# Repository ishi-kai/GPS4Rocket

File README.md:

# GPS System for Rocket
Commercially available GPS systems are not available for rockets.  
Therefore, we have created a full-scratch system.  

## Specification
- GPS Antenna
    - Use commercially available active antennas.
- [GPS Front End](https://github.com/ishi-kai/GPS4Rocket#GPS_FrontEnd)
    - MAX2769B-based GPS front-end board
- [Navigation Message Processor](https://github.com/ishi-kai/GPS4Rocket#Navigation_Message_Processor)
    - Operator to process IO data and navigation messages

## [GPS Front End Board](/GPS_FrontEnd/)
This is the hardware that handles the GPS front end. And This was created with KiCAD 9.  

## [Navigation Message Processor](/Navigation_Message_Processor/)

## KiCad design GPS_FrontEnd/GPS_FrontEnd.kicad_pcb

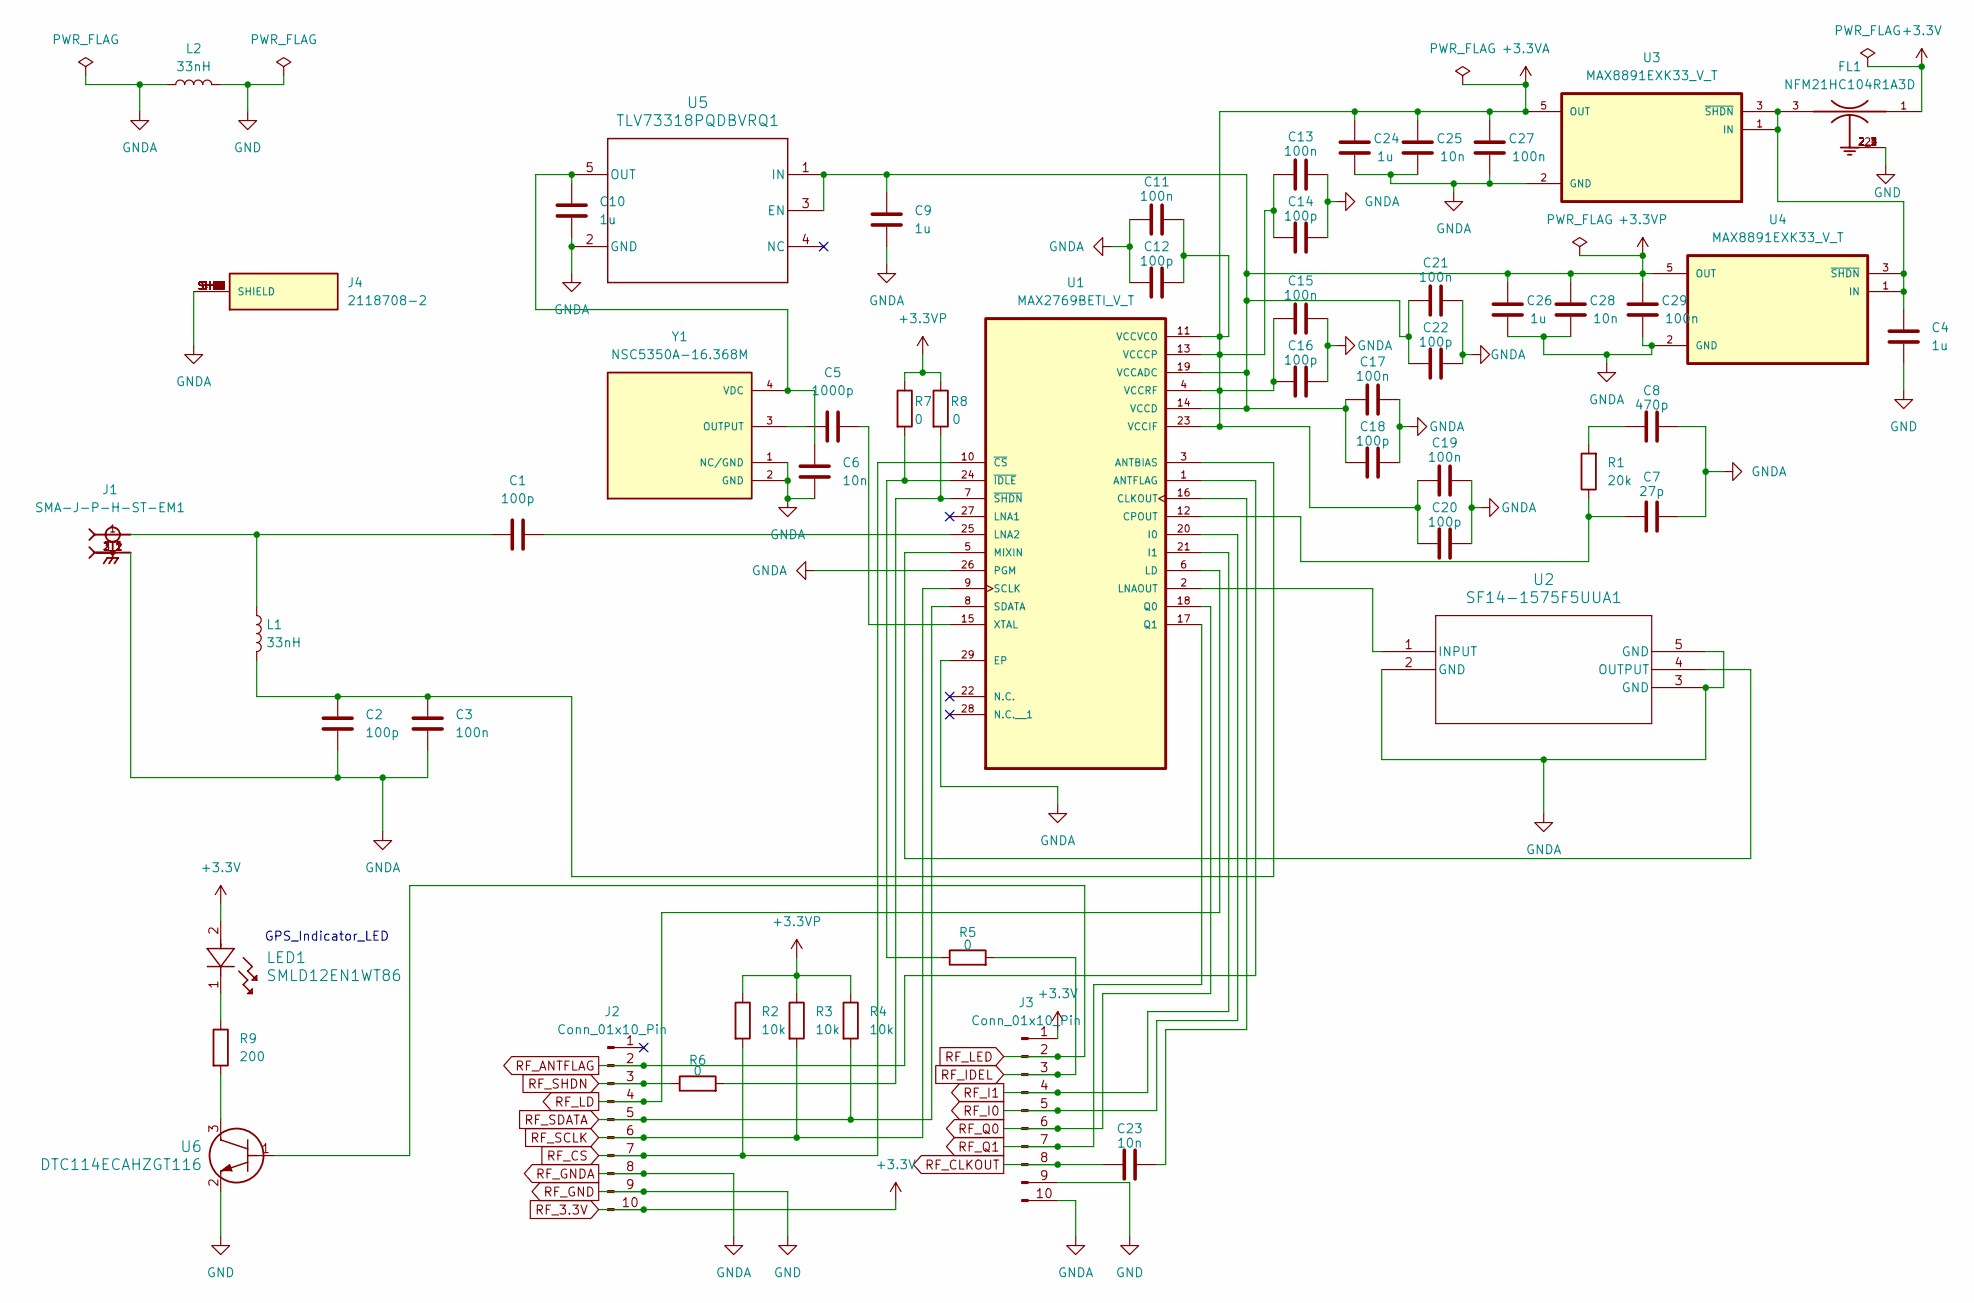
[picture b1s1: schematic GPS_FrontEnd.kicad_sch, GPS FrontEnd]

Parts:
C1, C2, C12, C14, C16, C18, C20, C22: 100p; C_0603_1608Metric
C3: 100n; C_1111_2828Metric
C4, C9, C10, C24, C26: 1u; C_0603_1608Metric
C5: 1000p; C_1210_3225Metric
C6: 10n; C_0505_1313Metric
C7: 27p; C_0603_1608Metric
C8: 470p; C_0505_1313Metric
C11, C13, C15, C17, C19, C21, C27, C29: 100n; C_0603_1608Metric
C23, C25, C28: 10n; C_0603_1608Metric
FL1: NFM21HC104R1A3D; FIL_NFM21HC104R1A3D
J1: SMA-J-P-H-ST-EM1; SAMTEC_SMA-J-P-H-ST-EM1; PARTREV G
J2, J3: Conn_01x10_Pin; PinHeader_1x10_P2.54mm_Vertical
J4: 2118708-2; TE_2118708-2; PARTREV A2
L1, L2: 33nH; L_0603_1608Metric
LED1: SMLD12EN1WT86
R1: 20k; R_0603_1608Metric
R2, R3, R4: 10k; R_0603_1608Metric
R5, R6, R7, R8: 0; R_0603_1608Metric
R9: 200; R_0603_1608Metric
U1: MAX2769BETI_V_T; QFN50P500X500X80-29N
U2: SF14-1575F5UUA1; SO4_1411-SAW_1p1x1p4_KAV
U3, U4: MAX8891EXK33_V_T; SOT65P210X110-5N
U5: TLV73318PQDBVRQ1; DBV0005A_N
U6: DTC114ECAHZGT116; TRANS_DTCZCAHZGT_ROM
Y1: NSC5350A-16.368M; OSC_TX22-18025S-19.200-R; PARTREV Nov 07, 2023

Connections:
+3.3VA: C11.2, C12.2, C13.2, C14.2, C15.1, C16.1, C19.1, C20.1, C24.1, C25.1, C27.1, U1.4 (VCCRF), U1.11 (VCCVCO), U1.13 (VCCCP), U1.23 (VCCIF), U3.5 (OUT)
+3.3VP: C9.1, C17.2, C18.2, C21.1, C22.1, C26.1, C28.1, C29.1, R2.1, R3.1, R4.1, R7.1, R8.1, U1.14 (VCCD), U1.19 (VCCADC), U4.5 (OUT), U5.1 (IN), U5.3 (EN)
unnamed: C1.1, J1.1, L1.1
unnamed: C8.1, R1.2
unnamed: LED1.1, R9.1
unnamed: R9.2, U6.3
unnamed: C2.1, C3.1, L1.2, U1.3 (ANTBIAS)
unnamed: C23.2, U1.16 (CLKOUT)
unnamed: C7.1, R1.1, U1.12 (CPOUT)
unnamed: C1.2, U1.25 (LNA2)
unnamed: U1.2 (LNAOUT), U2.1 (INPUT)
unnamed: U1.5 (MIXIN), U2.4 (OUTPUT)
unnamed: C5.2, U1.15 (XTAL)
unnamed: R5.1, R7.2, U1.24 (~IDLE)
unnamed: R6.2, R8.2, U1.7 (~SHDN)
unnamed: C4.1, FL1.3, U3.1 (IN), U3.3 (~SHDN), U4.1 (IN), U4.3 (~SHDN)
unnamed: C6.1, C10.1, U5.5 (OUT), Y1.4 (VDC)
unnamed: C5.1, Y1.3 (OUTPUT)
RF_3.3V: FL1.1, J2.10, J3.1, LED1.2
RF_ANTFLAG: J2.2, U1.1 (ANTFLAG)
RF_CLKOUT: C23.1, J3.8
RF_CS: J2.7, R2.2, U1.10 (~CS)
RF_GND: C4.2, FL1.2, FL1.2_1, FL1.2_2, FL1.2_3, FL1.2_4, J2.9, J3.9, L2.2, U6.2
RF_GNDA: C2.2, C3.2, C6.2, C7.2, C8.2, C9.2, C10.2, C11.1, C12.1, C13.1, C14.1, C15.2, C16.2, C17.1, C18.1, C19.2, C20.2, C21.2, C22.2, C24.2, C25.2, C26.2, C27.2, C28.2, C29.2, J1.2_1, J1.2_2, J1.3_1, J1.3_2, J2.8, J3.10, J4.SH1 (SHIELD), J4.SH2 (SHIELD), J4.SH3 (SHIELD), J4.SH4 (SHIELD), J4.SH5 (SHIELD), J4.SH6 (SHIELD), J4.SH7 (SHIELD), J4.SH8 (SHIELD), J4.SH9 (SHIELD), J4.SH10 (SHIELD), J4.SH11 (SHIELD), J4.SH12 (SHIELD), J4.SH13 (SHIELD), J4.SH14 (SHIELD), J4.SH15 (SHIELD), J4.SH16 (SHIELD), L2.1, U1.26 (PGM), U1.29 (EP), U2.2 (GND), U2.3 (GND), U2.5 (GND), U3.2 (GND), U4.2 (GND), U5.2 (GND), Y1.1 (NC/GND), Y1.2 (GND)
RF_I0: J3.5, U1.20 (I0)
RF_I1: J3.4, U1.21 (I1)
RF_IDEL: J3.3, R5.2
RF_LD: J2.4, U1.6 (LD)
RF_LED: J3.2, U6.1
RF_Q0: J3.6, U1.18 (Q0)
RF_Q1: J3.7, U1.17 (Q1)
RF_SCLK: J2.6, R3.2, U1.9 (SCLK)
RF_SDATA: J2.5, R4.2, U1.8 (SDATA)
RF_SHDN: J2.3, R6.1

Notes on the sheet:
GPS_Indicator_LED

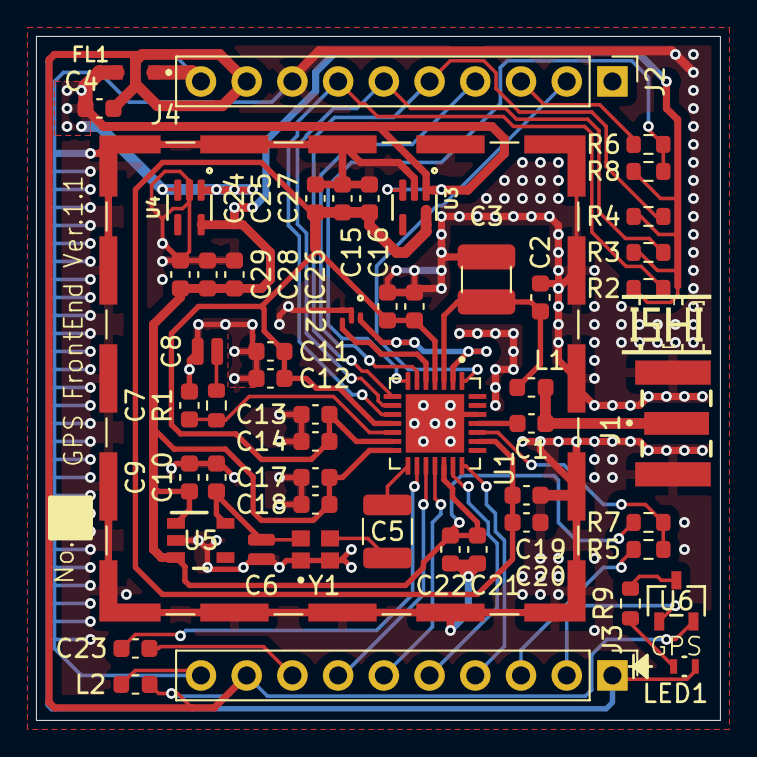
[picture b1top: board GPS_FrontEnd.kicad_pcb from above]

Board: 2 copper layers, 38.0 x 38.0 mm, 53 parts (0 on the bottom side), 34 nets.

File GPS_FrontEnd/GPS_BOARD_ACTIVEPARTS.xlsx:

出荷時に原産国が変わる場合があります。
表示されているHTSUSおよびECCN情報は情報提供のみを目的としたもので、分類の正確性や信頼性を表明または保証するものではありません。すべての情報は「現状の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
インデックス | メーカー品番 | メーカー名 | 商品概要 | リードタイム | 入手性 | 在庫状況 | 仕損率 | リクエスト数量1 | パック数量1 | パックタイプ1 | Digi-Key品番1 | 単価1 | 金額1 | 最小発注数量1 | 客先参照品番 | リクエスト品番 | リードタイム（週） | データシート | 参照名 | 米国輸入関税 | メモ | 部品状況 | RoHSステータス | 湿度感度レベル（MSL） | ECCN | HTSUS | 原産国 | 環境規制対応 | オリジナル品番 | 画像 | 製品に関する注意事項
1 | MAX2769BETI/V+T | Analog Devices Inc./Maxim Integrated | RF RCVR GPS 1575.42MHZ 28TQFN |  | 1,961 | 在庫品目 |  | 1 | 1 | Cut Tape (CT) | 175-MAX2769BETI/V+TCT-ND | 11.32000 | $11.32 | 1 |  | 175-MAX2769BETI/V+TCT-ND | 10 | https://mm.digikey.com/Volume0/opasdata/d220001/medias/docus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 |  | N/A |  | アクティブ | ROHS3対応 | 1（無制限） | 7A994 | 8542.39.0060 | Taiwan | https://www.maximintegrated.com/content/dam/files/design/emm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 | 175-MAX2769BETI/V+TCT-ND | https://mm.digikey.com/Volume0/opasdata/d220001/medias/image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 | キャンセルや返品はできません.
2 | MAX8891EXK33/V+T | Analog Devices Inc./Maxim Integrated | IC REG LINEAR 3.3V 150MA SC-70-6 |  | 3,895 | 在庫品目 |  | 2 | 2 | Cut Tape (CT) | 175-MAX8891EXK33/V+TCT-ND | 2.11000 | $4.22 | 1 |  | 175-MAX8891EXK33/V+TCT-ND | 10 | https://www.analog.com/media/en/technical-documentation/data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 |  | N/A |  | アクティブ | ROHS3対応 | 1（無制限） | EAR99 | 8542.39.0090 | Malaysia | https://www.maximintegrated.com/content/dam/files/design/emm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 | 175-MAX8891EXK33/V+TCT-ND | https://mm.digikey.com/Volume0/opasdata/d220001/medias/image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
3 | B39162B4348P810 | Qualcomm (RF front-end (RFFE) filters) | FILTER SAW 1.582GHZ 5-SMD |  | 778 | 在庫品目 |  | 1 | 1 | Cut Tape (CT) | B39162B4348P810CT-ND | 1.49000 | $1.49 | 1 |  | B39162B4348P810CT-ND | 8 | https://mm.digikey.com/Volume0/opasdata/d220001/medias/docus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 |  | N/A |  | アクティブ | ROHS3対応 | 2A（4週間） | EAR99 | 8541.60.0080 | Singapore |  | B39162B4348P810CT-ND | https://mm.digikey.com/Volume0/opasdata/d220001/medias/image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
4 | SMA-J-P-H-ST-EM1 | Samtec Inc. | CONN SMA JACK STR 50OHM EDGE MNT | 2025年10月16日に入荷予定：1個 | 0 | 通常在庫 |  | 1 | 1 | Tray | SAM8857-ND | 2.43000 | $2.43 | 1 |  | SAM8857-ND | 6 | https://mm.digikey.com/Volume0/opasdata/d220001/medias/docus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 |  | N/A |  | アクティブ | ROHS3対応 | 1（無制限） | EAR99 | 8536.69.4010 | Taiwan |  | SAM8857-ND | https://mm.digikey.com/Volume0/opasdata/d220001/medias/image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
5 | NSC5350A-16.368M | NDK (NIHON DEMPA KOGYO CO., LTD) | XTAL OSC TCXO 16.3680MHZ SMD |  | 867 | 在庫品目 |  | 1 | 1 | Cut Tape (CT) | 644-NSC5350A-16.368MCT-ND | 1.85000 | $1.85 | 1 |  | 644-NSC5350A-16.368MCT-ND | 24 | https://www.ndk.com/en/products/upload/lineup/pdf/NDKT03-000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 |  | N/A |  | アクティブ | ROHS3対応 | 2（1年間） | EAR99 | 8542.39.0090 | Japan |  | 644-NSC5350A-16.368MCT-ND | https://mm.digikey.com/Volume0/opasdata/d220001/medias/image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
6 | TLV73318PQDBVRQ1 | Texas Instruments | IC REG LINEAR 1.8V 300MA SOT23-5 |  | 16,868 | 在庫品目 |  | 1 | 1 | Cut Tape (CT) | 296-TLV73318PQDBVRQ1CT-ND | 0.45000 | $0.45 | 1 |  | 296-TLV73318PQDBVRQ1CT-ND | 12 | https://www.ti.com/general/docs/suppproductinfo.tsp?distId=1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 |  | N/A |  | アクティブ | ROHS3対応 | 1（無制限） | EAR99 | 8542.39.0090 | Philippines |  | 296-TLV73318PQDBVRQ1CT-ND | https://mm.digikey.com/Volume0/opasdata/d220001/medias/image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
7 | SF14-1575F5UUA1 | KYOCERA AVX | FILTER SAW 1.575GHZ 5-SMD |  | 8,991 | 個在庫あり - 非在庫保有商品 |  | 1 | 1 | Cut Tape (CT) | 478-SF14-1575F5UUA1CT-ND | 0.61000 | $0.61 | 1 |  | 478-SF14-1575F5UUA1CT-ND | 16 | https://mm.digikey.com/Volume0/opasdata/d220001/medias/docus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 |  | N/A |  | 生産中止品 | ROHS3対応 | 3（168時間） | 7A994 | 8541.60.0080 | Japan | https://ele.kyocera.com/assets/products/saw-device/environme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|ht… | 478-SF14-1575F5UUA1CT-ND | https://mm.digikey.com/Volume0/opasdata/d220001/medias/image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
8 | DTC114ECAHZGT116 | Rohm Semiconductor | TRANS PREBIAS NPN 0.1A SST3 |  | 2,933 | 在庫品目 |  | 1 | 1 | Cut Tape (CT) | DTC114ECAHZGT116CT-ND | 0.17000 | $0.17 | 1 |  | DTC114ECAHZGT116CT-ND | 18 | https://www.rohm.co.jp/datasheet?p=DTC114ECAHZG&dist=Digi-ke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 |  | N/A |  | アクティブ | ROHS3対応 | 1（無制限） | EAR99 | 8541.21.0075 | South Korea | https://fscdn.rohm.com/en/techdata_basic/transistor/anti_whi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 | DTC114ECAHZGT116CT-ND | https://mm.digikey.com/Volume0/opasdata/d220001/medias/image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
9 | 2118708-2 | TE Connectivity AMP Connectors | RF SHIELD 1.032"X1.032" SMD 1PC |  | 9,237 | 在庫品目 |  | 1 | 1 | Cut Tape (CT) | A126142CT-ND | 1.05000 | $1.05 | 1 |  | A126142CT-ND | 5 | https://www.te.com/commerce/DocumentDelivery/DDEController?A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 |  | N/A |  | アクティブ | RoHS対応 | 適用外 | EAR99 | 8529.90.9800 | China |  | A126142CT-ND | https://mm.digikey.com/Volume0/opasdata/d220001/medias/image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

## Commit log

2025-11-16 Add GPS Front End Board.
    Add GPS Front End Board.
